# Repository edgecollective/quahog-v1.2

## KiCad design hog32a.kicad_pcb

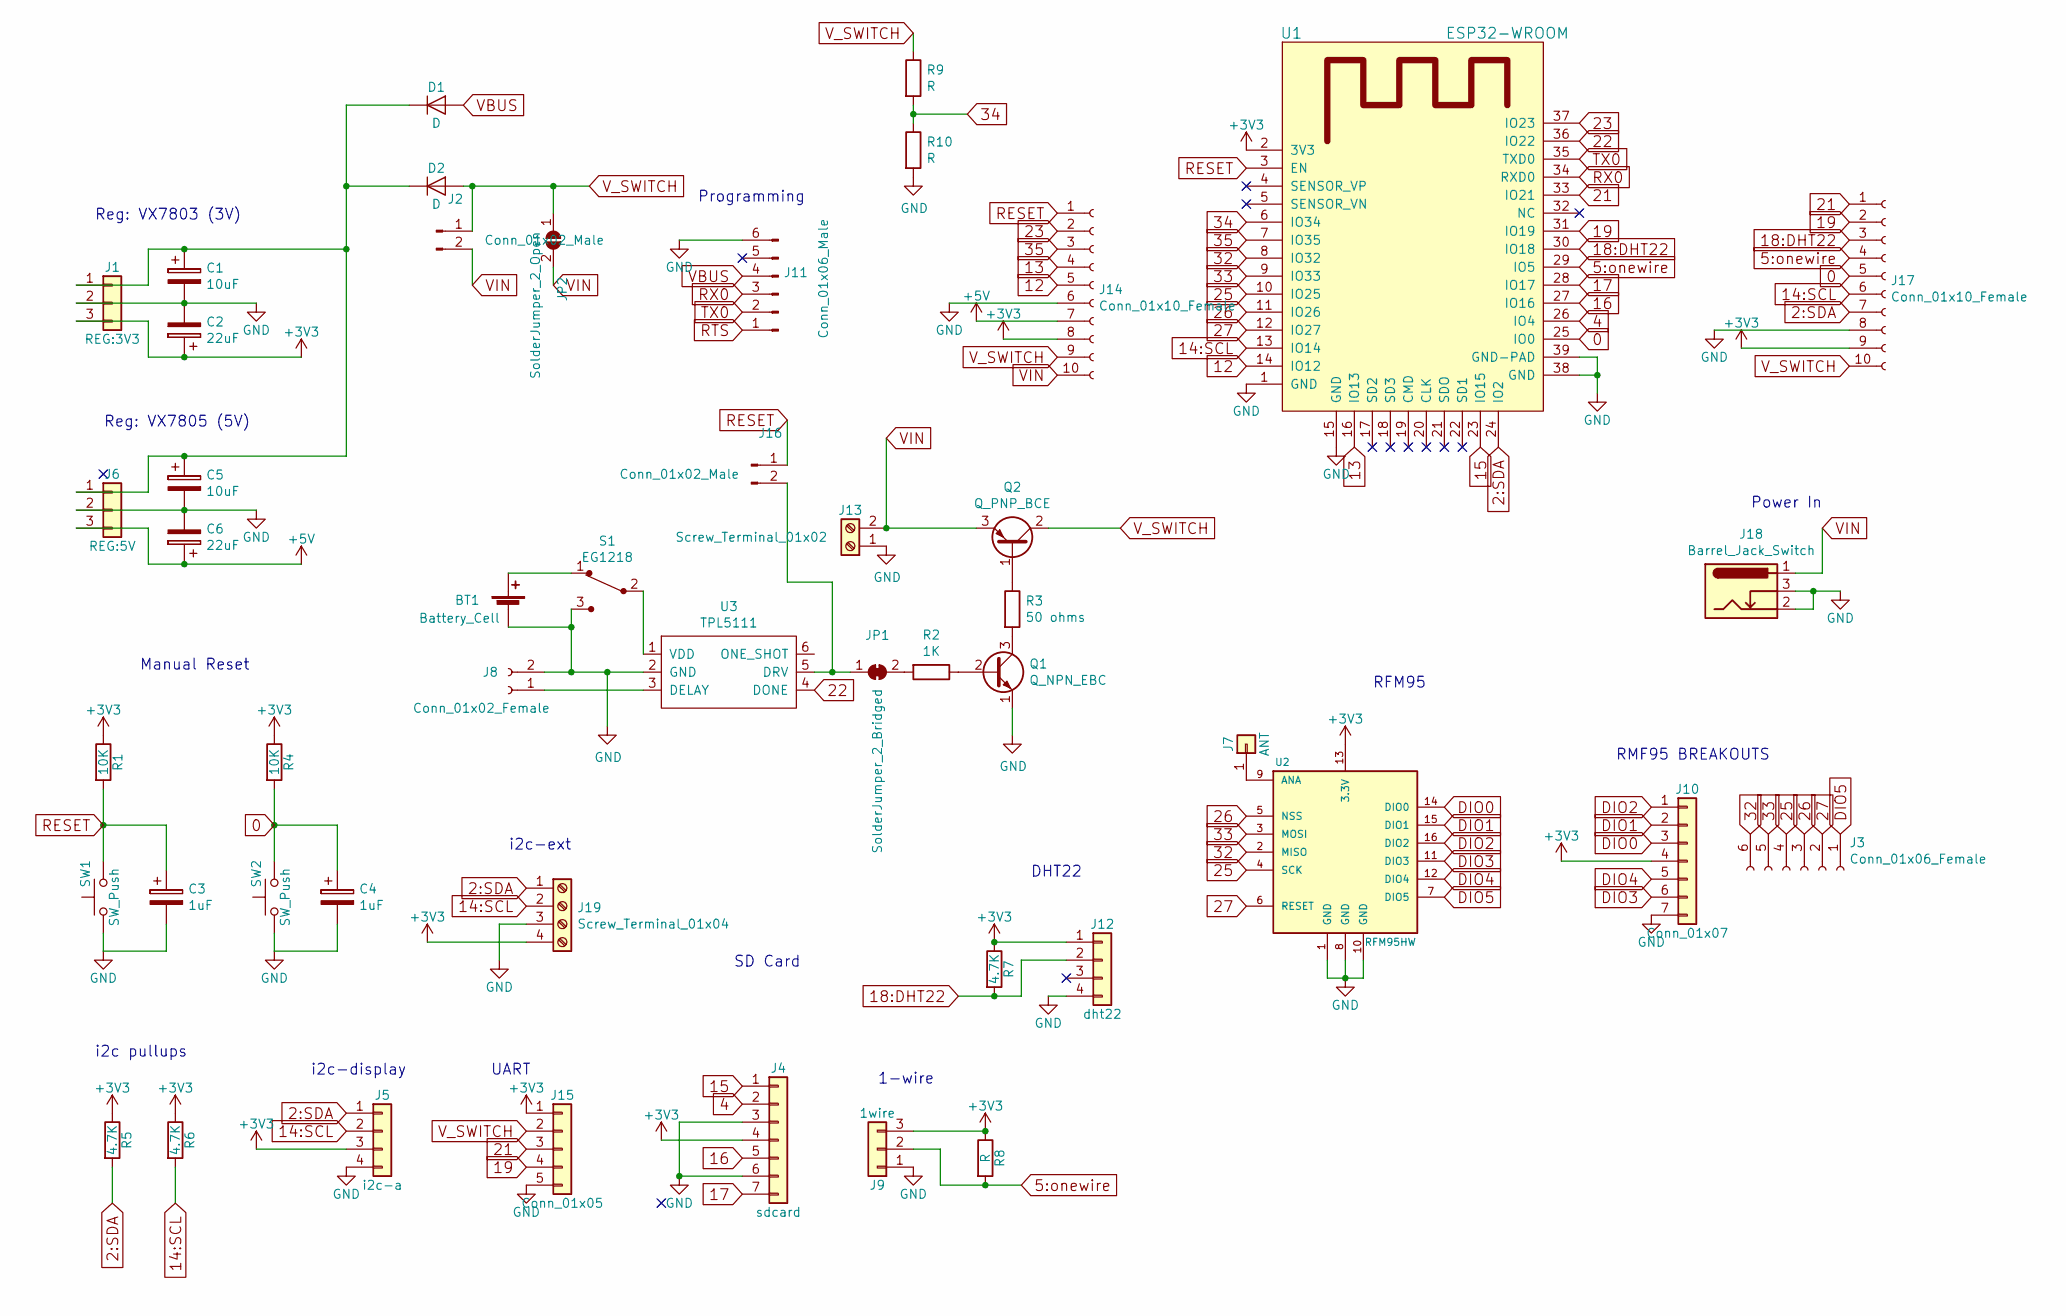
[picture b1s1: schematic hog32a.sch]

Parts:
BT1: Battery_Cell; BatteryHolder_Keystone_3000_1x12mm
C1, C5: 10uF; CP_Radial_D5.0mm_P2.50mm
C2, C6: 22uF; CP_Radial_D5.0mm_P2.50mm
C3, C4: 1uF; CP_Radial_D5.0mm_P2.50mm
D1, D2: D; D_DO-201_P5.08mm_Vertical_AnodeUp
J1: REG:3V3; Socket_Strip_Straight_1x03_Pitch2.54mm
J2, J16: Conn_01x02_Male; PinSocket_1x02_P2.54mm_Vertical
J3: Conn_01x06_Female; PinSocket_1x06_P2.54mm_Vertical
J4: sdcard; PinSocket_1x07_P2.54mm_Vertical
J5: i2c-a; Pin_Header_Straight_1x04_Pitch2.54mm
J6: REG:5V; Pin_Header_Straight_1x03_Pitch2.54mm
J7: ANT; Pin_Header_Straight_1x01_Pitch2.54mm
J8: Conn_01x02_Female; PinSocket_1x02_P2.54mm_Vertical
J9: 1wire; TerminalBlock_Phoenix_PT-3.5mm_3pol
J10: Conn_01x07; PinSocket_1x07_P2.54mm_Vertical
J11: Conn_01x06_Male; PinHeader_1x06_P2.54mm_Vertical
J12: dht22; Pin_Header_Straight_1x04_Pitch2.54mm
J13: Screw_Terminal_01x02; TerminalBlock_Phoenix_PT-1,5-2-3.5-H_1x02_P3.50mm_Horizontal
J14, J17: Conn_01x10_Female; PinSocket_1x10_P2.54mm_Vertical
J15: Conn_01x05; TerminalBlock_Phoenix_PT-3.5mm_5pol
J18: Barrel_Jack_Switch; BarrelJack_Horizontal
J19: Screw_Terminal_01x04; TerminalBlock_Phoenix_PT-1,5-4-3.5-H_1x04_P3.50mm_Horizontal
JP1: SolderJumper_2_Bridged; SolderJumper-2_P1.3mm_Bridged_RoundedPad1.0x1.5mm
JP2: SolderJumper_2_Open; SolderJumper-2_P1.3mm_Open_RoundedPad1.0x1.5mm
Q1: Q_NPN_EBC; TO-92
Q2: Q_PNP_BCE; TO-220-3_Vertical
R1, R4: 10K; R_Axial_DIN0204_L3.6mm_D1.6mm_P1.90mm_Vertical
R2: 1K; R_Axial_DIN0204_L3.6mm_D1.6mm_P1.90mm_Vertical
R3: 50 ohms; R_Axial_DIN0204_L3.6mm_D1.6mm_P1.90mm_Vertical
R5, R6, R7: 4.7K; R_Axial_DIN0204_L3.6mm_D1.6mm_P1.90mm_Vertical
R8, R9, R10: R; R_Axial_DIN0204_L3.6mm_D1.6mm_P1.90mm_Vertical
S1: EG1218; Switch_Slide_11.6x4mm_EG1218; MPN EG1218; Digi-Key_PN EG1903-ND
SW1, SW2: SW_Push; SW_PUSH_6mm
U1: ESP32-WROOM
U2: RFM95HW; RFM95
U3: TPL5111; SOT-23-6_Handsoldering

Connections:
0: C4.1, J17.5, R4.2, SW2.2, U1.25 (IO0)
2:SDA: J5.1, J17.7, J19.1, R5.2, U1.24 (IO2)
4: J4.2, U1.26 (IO4)
5:onewire: J9.2, J17.4, R8.2, U1.29 (IO5)
12: J14.5, U1.14 (IO12)
13: J14.4, U1.16 (IO13)
14:SCL: J5.2, J17.6, J19.2, R6.2, U1.13 (IO14)
15: J4.1, U1.23 (IO15)
16: J4.5, U1.27 (IO16)
17: J4.7, U1.28 (IO17)
18:DHT22: J12.2, J17.3, R7.2, U1.30 (IO18)
19: J15.4, J17.2, U1.31 (IO19)
21: J15.3, J17.1, U1.33 (IO21)
22: U1.36 (IO22), U3.4 (DONE)
23: J14.2, U1.37 (IO23)
25: J3.4, U1.10 (IO25), U2.4 (SCK)
26: J3.3, U1.11 (IO26), U2.5 (NSS)
27: J3.2, U1.12 (IO27), U2.6 (RESET)
32: J3.6, U1.8 (IO32), U2.2 (MISO)
33: J3.5, U1.9 (IO33), U2.3 (MOSI)
34: R9.2, R10.1, U1.6 (IO34)
35: J14.3, U1.7 (IO35)
+3V3: C2.1, J1.3, J4.4, J5.3, J9.3, J10.4, J12.1, J14.8, J15.1, J17.9, J19.4, R1.1, R4.1, R5.1, R6.1, R7.1, R8.1, U1.2 (3V3), U2.13 (3.3V)
+5V: C6.1, J6.3, J14.7
DIO0: J10.3, U2.14 (DIO0)
DIO1: J10.2, U2.15 (DIO1)
DIO2: J10.1, U2.16 (DIO2)
DIO3: J10.6, U2.11 (DIO3)
DIO4: J10.5, U2.12 (DIO4)
DIO5: J3.1, U2.7 (DIO5)
GND: BT1.2 (-), C1.2, C2.2, C3.2, C4.2, C5.2, C6.2, J1.2, J4.3, J4.6, J5.4, J6.2, J8.2, J9.1, J10.7, J11.6, J12.4, J13.1, J14.6, J15.5, J17.8, J18.2, J18.3, J19.3, Q1.1 (E), R10.2, S1.3, SW1.1, SW2.1, U1.1 (GND), U1.15 (GND), U1.38 (GND), U1.39 (GND-PAD), U2.1 (GND), U2.8 (GND), U2.10 (GND), U3.2 (GND)
unnamed: BT1.1 (+), S1.1
unnamed: C1.1, C5.1, D1.1 (K), D2.1 (K), J1.1, J6.1
unnamed: J7.1, U2.9 (ANA)
unnamed: J8.1, U3.3 (DELAY)
unnamed: J16.2, JP1.1 (A), U3.5 (DRV)
unnamed: JP1.2 (B), R2.2
unnamed: Q1.2 (B), R2.1
unnamed: Q1.3 (C), R3.2
unnamed: Q2.1 (B), R3.1
unnamed: S1.2, U3.1 (VDD)
RESET: C3.1, J14.1, J16.1, R1.2, SW1.2, U1.3 (EN)
RX0: J11.3, U1.34 (RXD0)
TX0: J11.2, U1.35 (TXD0)
VBUS: D1.2 (A), J11.4
VIN: J2.2, J13.2, J14.10, J18.1, JP2.2 (B), Q2.3 (E)
V_SWITCH: D2.2 (A), J2.1, J14.9, J15.2, J17.10, JP2.1 (A), Q2.2 (C), R9.1

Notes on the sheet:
SD Card
i2c-display
i2c pullups
Programming
1-wire
Power In
Reg: VX7805 (5V)
DHT22
UART
RFM95
RMF95 BREAKOUTS
Reg: VX7803 (3V)
Manual Reset
i2c-ext

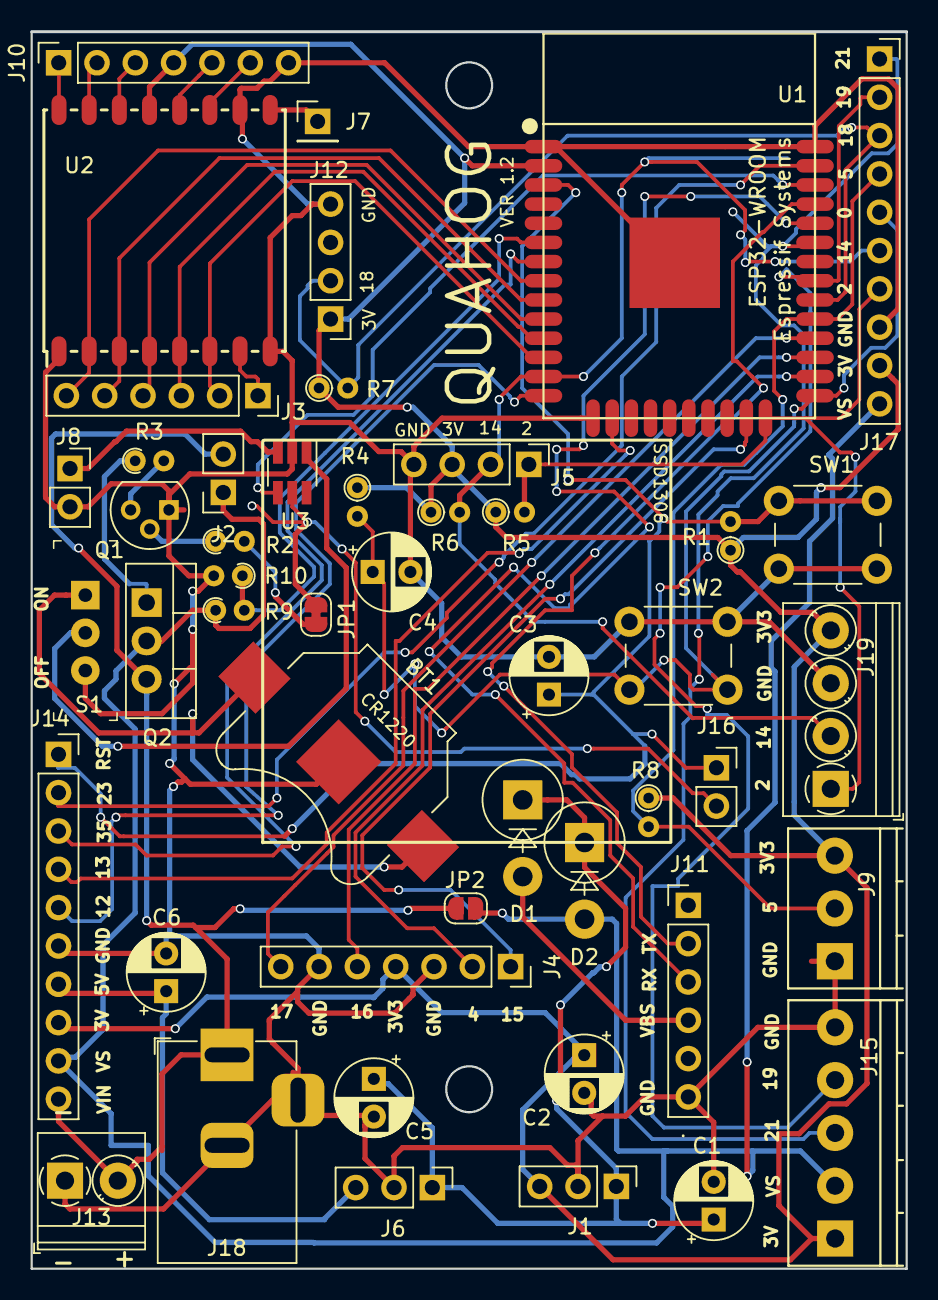
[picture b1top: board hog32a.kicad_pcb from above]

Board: 2 copper layers, 58.0 x 82.0 mm, 48 parts (0 on the bottom side), 47 nets.

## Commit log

2019-05-20 update;
